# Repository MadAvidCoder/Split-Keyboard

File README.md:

# Split Keyboard
An ergonomic, wireless, split, low-profile keyboard I made for [Hack Club](https://hackclub.com/) [Blueprint](https://blueprint.hackclub.com/r/43?ref=r)! It is inspired by the Lily58 layout, but with column-staggering better optimised for my hands. It also features a thumb cluster designed for better ergonomics. Having recently started using a Mechcanical Keyboard, I was keen to design a Split Keyboard that was easy to transition to, so I elected to include a number row, and an additional 'function' column on each half.

You can read about my development journey [here](https://blueprint.hackclub.com/projects/10297).

## Key Features
- Wireless
- Split
- Customisable ZMK Firmware
- Column Staggered
- 54 Keys
- Thumb Clusters
- Low Profile Choc Switches
- RGB Backlight

## PCB
I designed the PCB using KiCad. I kept it simple, with only 2 layers. The two halves are (mostly) mirror-images of each other, and I used hierarchical sheets to easily keep the design matching.

### Schematic

### PCB Design
| Left | Right |
|------|------|
|||

## Firmware
I am using [ZMK Firmware](https://zmk.dev/) for this keyboard. The configuration files are in their own repo, linked to the `firmware` directory. I chose to keep the keymap simple, to make it easy to transition to from a standard keyboard. I have also included minimal extra features and config, as I want to experiment with that side of things, once I have actually built it.

## Case
I designed the case for the keyboard in Autodesk Fusion 360. It is a fairly simple design, which secures the PCB via 5 screws, and has a top plate to hold it all in place. The top half is secured with a number of locating pins. The two halves of the case are nearly identical, except for different placement of the capacitor cutout.

The case also features a cutout and location for the LiPo battery, so it can be easily secured. USB and charging access is via the edge above the thumb cluster.

|Top|Bottom|
|---|------|
|||

### Render

### Keycaps
To ensure they work well, I am using keycaps designed by other people. For the main keycaps, I am using the [LPX profile keycaps](https://github.com/levpopov/LPX), designed by [levpopov](https://github.com/levpopov).

For the thumb clusters, I have selected the [Choc Louder Keycaps](https://www.printables.com/model/1066117-choc-louder-keycaps-choc-and-mx-spacing) by [kooziecup](https://www.printables.com/@koozie). The dimpled profile should make them more comfortable for the thumbs to rest on.

## BOM
A more detailed csv BOM can be found in [BOM.csv](/BOM.csv). All prices are in USD, and rounded to 2 decimal places (although the total is based on un-rounded prices).

In some cases, items may have higher quantities than are actually needed, due to MOQ. However, I have done thorough research to ensure that these still work out as the cheapest option.

| Item                    | Qty. | Price (USD) | Ext. Price (USD) | Link                                                  |
|-------------------------|------|-------------|------------------|-------------------------------------------------------|
| PCB                     | 1    | 12.55       | 12.55            | https://jlcpcb.com/                                   |
| Battery                 | 2    | 5.80        | 11.60            | https://ecocell.com.au/product/lipo-600-503040/       |
| nice!nano               | 2    | 4.55        | 9.10             | https://www.aliexpress.com/item/1005007266900944.html |
| Hotswap Sockets         | 70   | 0.11        | 7.70             | https://www.aliexpress.com/item/1005009312876316.html |
| Switches                | 60   | 0.46        | 27.60            | https://www.aliexpress.com/item/1005008751312031.html |
| SK6812-MINI-E           | 55   | 0.07        | 3.85             | https://www.lcsc.com/product-detail/C5149201.html     |
| DMBJ PNLS8040-100M 10UH | 5    | 0.11        | 0.55             | https://www.lcsc.com/product-detail/C2849554.html     |
| 100nF Capacitor         | 100  | 0.01        | 1.00             | https://www.lcsc.com/product-detail/C49678.html       |
| 10uF Capacitor          | 10   | 0.02        | 0.20             | https://www.lcsc.com/product-detail/C32635.html       |
| 22uF Capacitor          | 10   | 0.02        | 0.20             | https://www.lcsc.com/product-detail/C98190.html       |
| 470uF Capacitor         | 10   | 0.04        | 0.40             | https://www.lcsc.com/product-detail/C2858856.html     |
| 1N5819 Diode            | 100  | 0.01        | 1.00             | https://www.lcsc.com/product-detail/C963381.html      |
| SS34 Schottky Diode     | 10   | 0.03        | 0.30             | https://www.lcsc.com/product-detail/C842788.html      |
| 806k Resistor           | 20   | <0.01       | 0.09             | https://www.lcsc.com/product-detail/C865659.html      |
| 2M Resistor             | 100  | <0.01       | 0.25             | https://www.lcsc.com/product-detail/C26112.html       |
| 470R Resistor           | 100  | <0.01       | 0.17             | https://www.lcsc.com/product-detail/C2907267.html     |
| 2k Resistor             | 100  | <0.01       | 0.18             | https://www.lcsc.com/product-detail/C2907248.html     |
| 10k Resistor            | 10   | 0.04        | 0.40             | https://www.lcsc.com/product-detail/C319942.html      |
| 73.2k Resistor          | 50   | 0.01        | 0.50             | https://www.lcsc.com/product-detail/C422816.html      |
| 330R Resistor           | 100  | <0.01       | 0.13             | https://www.lcsc.com/product-detail/C2907321.html     |
| DW01A                   | 20   | 0.02        | 0.40             | https://www.lcsc.com/product-detail/C18164398.html    |
| FS8205                  | 10   | 0.05        | 0.50             | https://www.lcsc.com/product-detail/C2830320.html     |
| MT3608                  | 10   | 0.06        | 0.60             | https://www.lcsc.com/product-detail/C84817.html       |
| LCSC Shipping           | 1    | 12.72       | 12.72            | https://www.lcsc.com/                                 |
| EcoCell Shipping        | 1    | 2.78        | 2.78             | https://ecocell.com.au/                               |
|                         |      |             |                  |                                                       |
| **TOTAL**               |      |             |                  | **$93.95 (USD)**                                      |

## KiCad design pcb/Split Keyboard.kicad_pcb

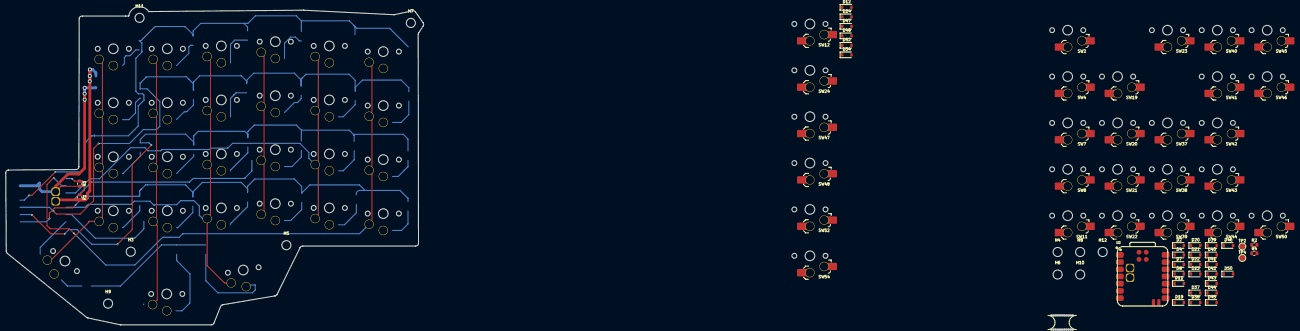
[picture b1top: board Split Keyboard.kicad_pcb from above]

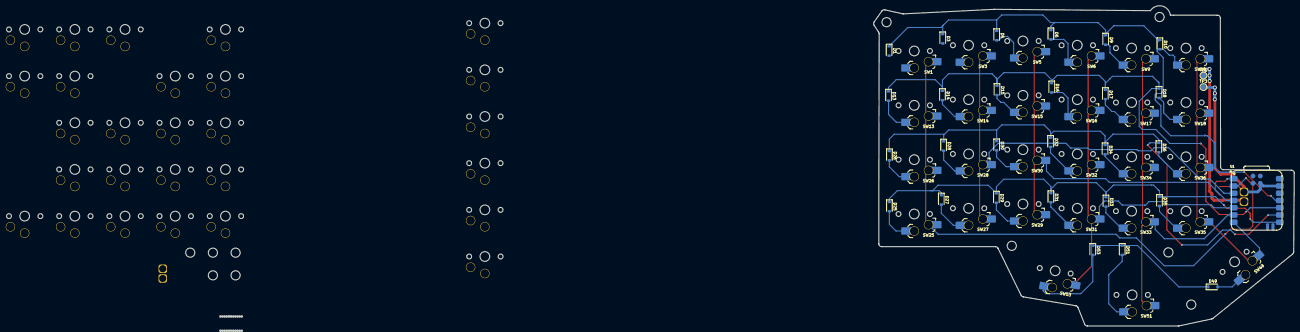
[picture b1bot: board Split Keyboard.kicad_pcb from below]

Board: 2 copper layers, 147.4 x 112.2 mm, 131 parts (57 on the bottom side), 80 nets.

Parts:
D1, D2, D3, D4, D5, D6, D7, D8, D9, D10, D11, D12, D13, D14, D15, D16, D17, D18, D19, D20, D21, D22, D23, D24, D25, D26, D27, D28, D29, D30, D31, D32, D33, D34, D35, D36, D37, D38, D39, D40, D41, D42, D43, D44, D45, D46, D47, D48, D49, D50, D51, D52, D53, D54: D; D_SOD-123
H1, H2, H15: MountingHole; mouse-bite-5mm-slot
H3, H4, H5, H6, H7, H8, H9, H10, H11, H12: MountingHole; MountingHole_3.2mm_M3
R1, R2: 806k; R_0805_2012Metric
R3, R4: 2M; R_0805_2012Metric
SW1, SW2, SW3, SW4, SW5, SW6, SW7, SW8, SW9, SW10, SW11, SW12, SW13, SW14, SW15, SW16, SW17, SW18, SW19, SW20, SW21, SW22, SW23, SW24, SW25, SW26, SW27, SW28, SW29, SW30, SW31, SW32, SW33, SW34, SW35, SW36, SW37, SW38, SW39, SW40, SW41, SW42, SW43, SW44, SW45, SW46, SW47, SW48, SW53, SW54: SW_Push; SW_choc_v1_HS_CPG135001S30_1u
SW49, SW50: SW_Push; SW_choc_v1_HS_CPG135001S30_1.75u
SW51, SW52: SW_Push; SW_choc_v1_HS_CPG135001S30_1.5u
TP1, TP2: BAT; TestPoint_Pad_D2.0mm
TP3, TP4: GND; TestPoint_Pad_D2.0mm
U1, U2: XIAO-nRF52840-SMD; modified-XIAO-nRF52840-SMD

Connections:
/Left/BAT_SENSE: R1.1, R3.1, U1.1 (P0.02_A0_D0)
/Left/COL0: SW1.1, SW13.1, SW25.1, SW26.1, U1.2 (P0.03_A1_D1)
/Left/COL1: SW3.1, SW14.1, SW27.1, SW28.1, U1.3 (P0.28_A2_D2)
/Left/COL2: SW5.1, SW15.1, SW29.1, SW30.1, U1.4 (P0.29_A3_D3)
/Left/COL3: SW6.1, SW16.1, SW31.1, SW32.1, SW53.1, U1.5 (P0.04_A4_D4_SDA)
/Left/COL4: SW9.1, SW17.1, SW33.1, SW34.1, SW51.1, U1.6 (P0.05_A5_D5_SCL)
/Left/COL5: SW10.1, SW18.1, SW35.1, SW36.1, SW49.1, U1.7 (P1.11_D6_TX)
/Left/ROW0: D1.1 (K), D3.1 (K), D5.1 (K), D6.1 (K), D9.1 (K), D10.1 (K), U1.11 (P1.15_D10_MOSI)
/Left/ROW1: D13.1 (K), D14.1 (K), D15.1 (K), D16.1 (K), D17.1 (K), D18.1 (K), U1.10 (P1.14_D9_MISO)
/Left/ROW2: D26.1 (K), D28.1 (K), D30.1 (K), D32.1 (K), D34.1 (K), D36.1 (K), U1.9 (P1.13_D8_SCK)
/Left/ROW3: D25.1 (K), D27.1 (K), D29.1 (K), D31.1 (K), D33.1 (K), D35.1 (K), U1.8 (P1.12_D7_RX)
/Left/ROW4: D49.1 (K), D51.1 (K), D53.1 (K)
/Right/BAT_SENSE: R2.1, R4.1, U2.1 (P0.02_A0_D0)
/Right/COL0: SW2.1, SW19.1, SW37.1, SW38.1, U2.2 (P0.03_A1_D1)
/Right/COL1: SW4.1, SW20.1, SW39.1, SW40.1, U2.3 (P0.28_A2_D2)
/Right/COL2: SW7.1, SW21.1, SW41.1, SW42.1, U2.4 (P0.29_A3_D3)
/Right/COL3: SW8.1, SW22.1, SW43.1, SW44.1, SW54.1, U2.5 (P0.04_A4_D4_SDA)
/Right/COL4: SW11.1, SW23.1, SW45.1, SW46.1, SW52.1, U2.6 (P0.05_A5_D5_SCL)
/Right/COL5: SW12.1, SW24.1, SW47.1, SW48.1, SW50.1, U2.7 (P1.11_D6_TX)
/Right/ROW0: D2.1 (K), D4.1 (K), D7.1 (K), D8.1 (K), D11.1 (K), D12.1 (K), U2.11 (P1.15_D10_MOSI)
/Right/ROW1: D19.1 (K), D20.1 (K), D21.1 (K), D22.1 (K), D23.1 (K), D24.1 (K), U2.10 (P1.14_D9_MISO)
/Right/ROW2: D38.1 (K), D40.1 (K), D42.1 (K), D44.1 (K), D46.1 (K), D48.1 (K), U2.9 (P1.13_D8_SCK)
/Right/ROW3: D37.1 (K), D39.1 (K), D41.1 (K), D43.1 (K), D45.1 (K), D47.1 (K), U2.8 (P1.12_D7_RX)
/Right/ROW4: D50.1 (K), D52.1 (K), D54.1 (K)
GND: R3.2, R4.2, TP3.1, TP4.1, U1.13 (GND), U1.16 (GND), U1.22 (GND), U2.13 (GND), U2.16 (GND), U2.22 (GND)
unnamed: D1.2 (A), SW1.2
unnamed: D2.2 (A), SW2.2
unnamed: D3.2 (A), SW3.2
unnamed: D4.2 (A), SW4.2
unnamed: D5.2 (A), SW5.2
unnamed: D6.2 (A), SW6.2
unnamed: D7.2 (A), SW7.2
unnamed: D8.2 (A), SW8.2
unnamed: D9.2 (A), SW9.2
unnamed: D10.2 (A), SW10.2
unnamed: D11.2 (A), SW11.2
unnamed: D12.2 (A), SW12.2
unnamed: D13.2 (A), SW13.2
unnamed: D14.2 (A), SW14.2
unnamed: D15.2 (A), SW15.2
unnamed: D16.2 (A), SW16.2
unnamed: D17.2 (A), SW17.2
unnamed: D18.2 (A), SW18.2
unnamed: D19.2 (A), SW19.2
unnamed: D20.2 (A), SW20.2
unnamed: D21.2 (A), SW21.2
unnamed: D22.2 (A), SW22.2
unnamed: D23.2 (A), SW23.2
unnamed: D24.2 (A), SW24.2
unnamed: D25.2 (A), SW25.2
unnamed: D26.2 (A), SW26.2
unnamed: D27.2 (A), SW27.2
unnamed: D28.2 (A), SW28.2
unnamed: D29.2 (A), SW29.2
unnamed: D30.2 (A), SW30.2
unnamed: D31.2 (A), SW31.2
unnamed: D32.2 (A), SW32.2
unnamed: D33.2 (A), SW33.2
unnamed: D34.2 (A), SW34.2
unnamed: D35.2 (A), SW35.2
unnamed: D36.2 (A), SW36.2
unnamed: D37.2 (A), SW37.2
unnamed: D38.2 (A), SW38.2
unnamed: D39.2 (A), SW39.2
unnamed: D40.2 (A), SW40.2
unnamed: D41.2 (A), SW41.2
unnamed: D42.2 (A), SW42.2
unnamed: D43.2 (A), SW43.2
unnamed: D44.2 (A), SW44.2
unnamed: D45.2 (A), SW45.2
unnamed: D46.2 (A), SW46.2
unnamed: D47.2 (A), SW47.2
unnamed: D48.2 (A), SW48.2
unnamed: D49.2 (A), SW49.2
unnamed: D50.2 (A), SW50.2
unnamed: D51.2 (A), SW51.2
unnamed: D52.2 (A), SW52.2
unnamed: D53.2 (A), SW53.2
unnamed: D54.2 (A), SW54.2
VBAT: R1.2, R2.2, TP1.1, TP2.1, U1.15 (BAT), U2.15 (BAT)

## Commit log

2026-01-20 Create KiCad Project
    Created the main kicad project
2026-01-20 Update gitignore
    Updated the gitignore file to include Kicad temporary lock files
2026-01-20 Create Schematics
    Created the blank schematic, ready to be edited
2026-01-20 Design schematic
    I designed the base schematic for the keyboard, and assigned parts and footprints for everything
2026-01-21 Add BMS and LEDs
    Added a Battery Management system and some RGB LED backlight
2026-01-22 Add other half
    Designed, Placed and Routed the other half of the PCB
2026-01-24 Finished Designing PCB
    Finished Desiging the PCB and exported gerbers for manufacturing
2026-01-25 Export Schematic
    Exported the Schematic to a PDF for easier review
2026-01-25 Add firmware submodule
    Added a submodule for the zmk firmware
2026-01-25 Sync firmware
    Synced the firmware submodule
2026-01-25 Add 3d models
    Added 3d models to the PCB and exported
2026-01-26 Add Case
    Added the CAD files for the case
2026-01-26 Add README
    Added a README to document the project
2026-01-26 Add BOMs
    Added the BOM for the project
2026-01-26 Add total cost
    Added the total cost to the BOM
